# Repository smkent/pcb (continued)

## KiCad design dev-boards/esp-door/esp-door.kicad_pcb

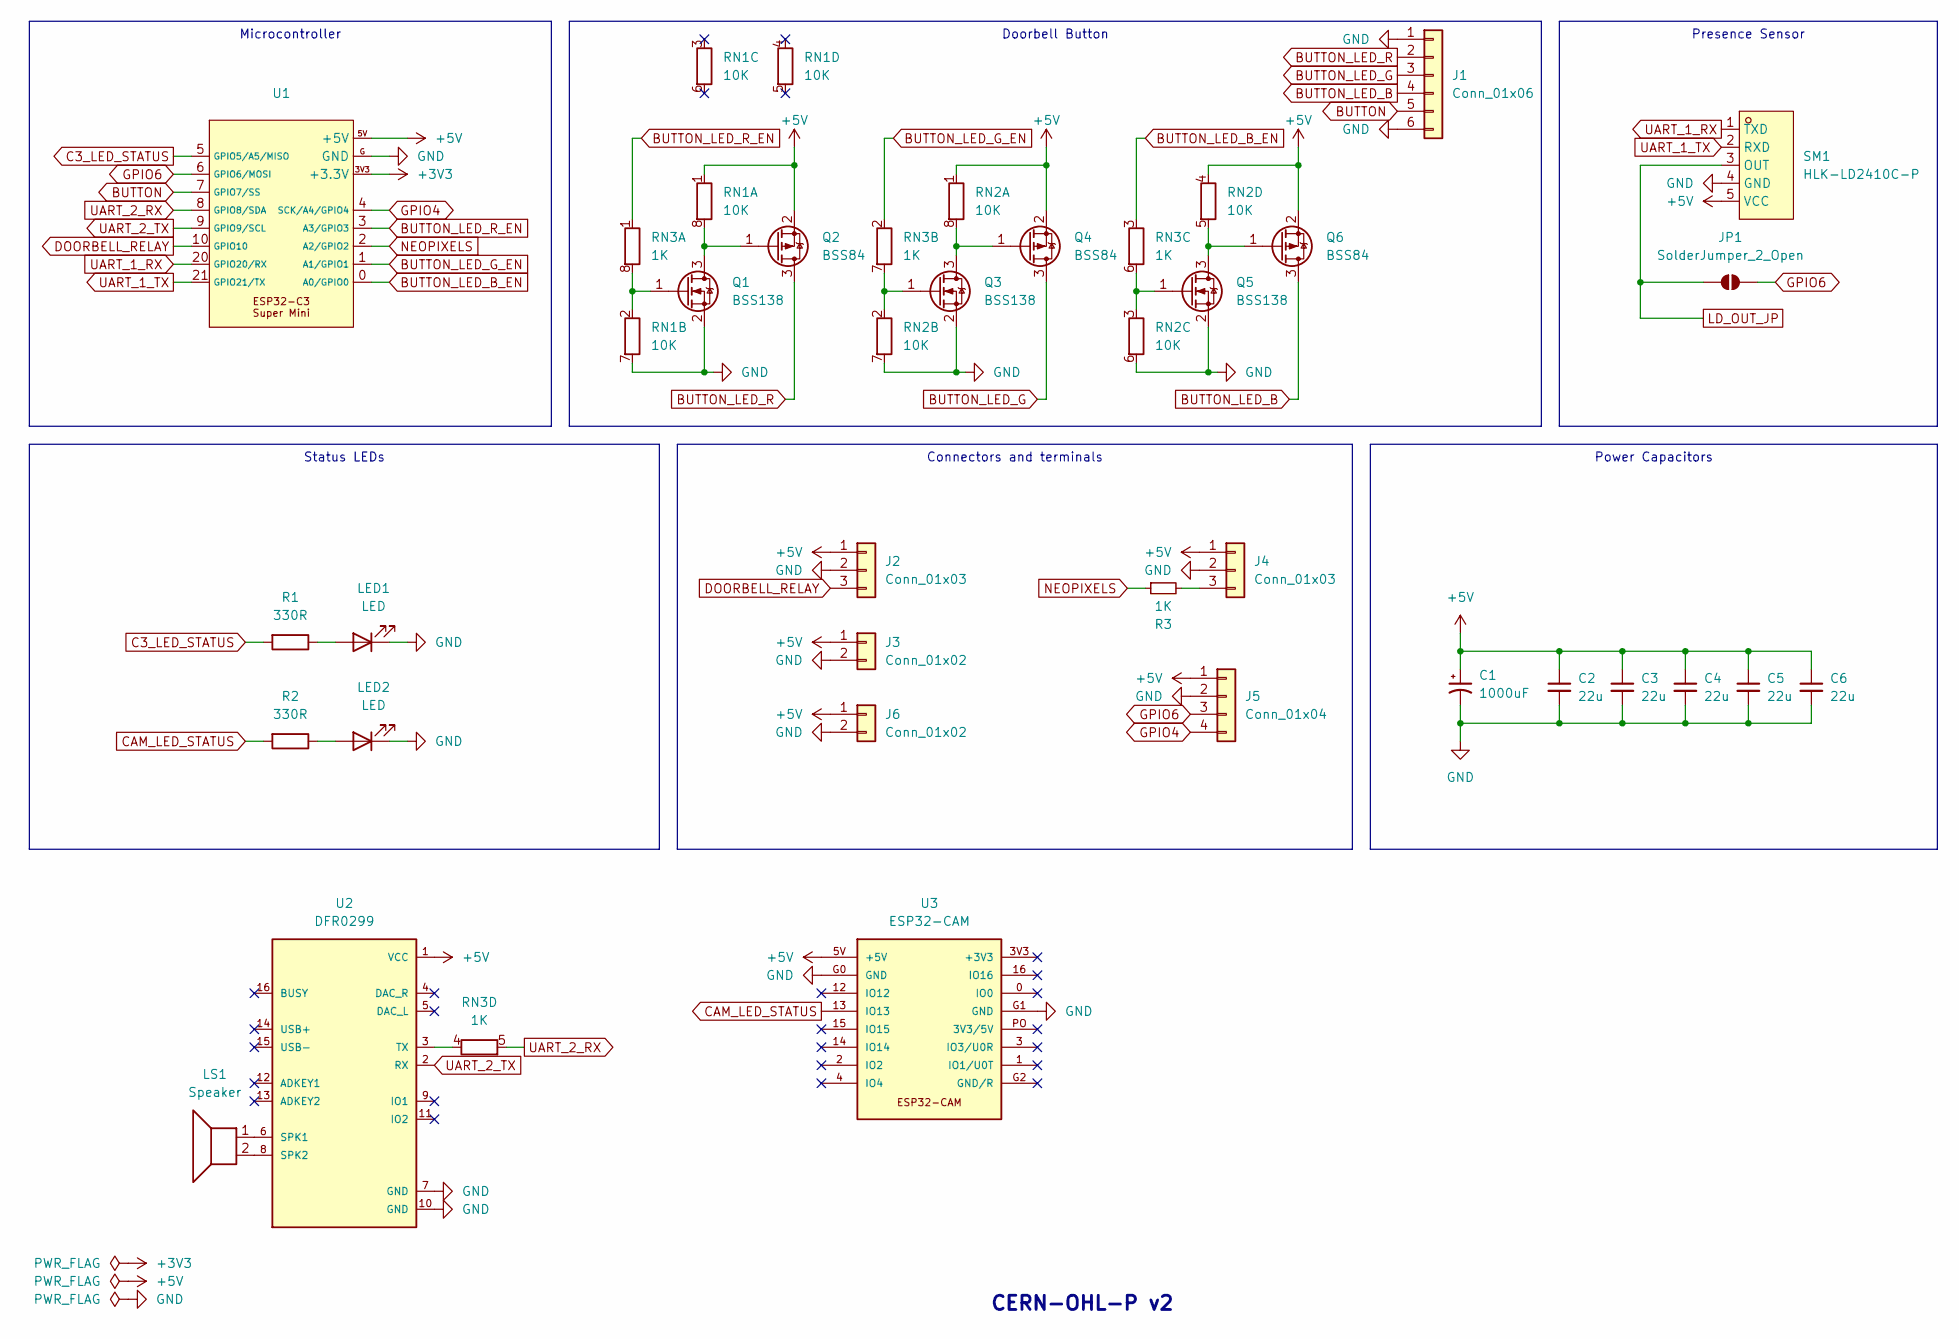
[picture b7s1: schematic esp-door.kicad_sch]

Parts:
C1: 1000uF; CP_Elec_8x10.5
C2, C3, C4, C5, C6: 22u; C_1206_3216Metric_Pad1.33x1.80mm_HandSolder
J1: Conn_01x06; JST_XH_S6B-XH_1x06_P2.50mm_Horizontal
J2, J4: Conn_01x03; JST_XH_S3B-XH_1x03_P2.50mm_Horizontal_pad2gnd
J3: Conn_01x02; JST_XH_S2B-XH_1x02_P2.50mm_Horizontal
J5: Conn_01x04; SurfacePads_1x04_P2.54mm_pad2gnd
J6: Conn_01x02; SurfacePads_1x02_P2.54mm_pad2gnd
JP1: SolderJumper_2_Open; SolderJumper-2_P1.3mm_Open_TrianglePad1.0x1.5mm
LED1, LED2: LED; LED_0805_2012Metric_Pad1.15x1.40mm_HandSolder_simple
LS1: Speaker; JST_XH_S2B-XH_1x02_P2.50mm_Horizontal
Q1, Q3, Q5: BSS138; SOT-23_simple
Q2, Q4, Q6: BSS84; SOT-23_simple
R1, R2: 330R; R_0805_2012Metric_Pad1.20x1.40mm_HandSolder
R3: 1K; R_0805_2012Metric_Pad1.20x1.40mm_HandSolder
RN1, RN2: 10K; R_Array_Convex_4x0603
RN3: 1K; R_Array_Convex_4x0603
SM1: HLK-LD2410C-P; SENSOR-TH_HLK-LD2410C-P; LCSC Part C19723500
U1: ESP32-C3-Super-Mini-Castellated-SMD
U2: DFR0299; DFPlayer-Mini-DFR0299-module
U3: ESP32-CAM

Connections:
+3V3: U1.3V3 (+3.3V)
+5V: C1.1, C2.1, C3.1, C4.1, C5.1, C6.1, J2.1, J3.1, J4.1, J5.1, J6.1, Q2.2 (S), Q4.2 (S), Q6.2 (S), RN1.1 (R1.1), RN2.1 (R1.1), RN2.4 (R4.1), SM1.5 (VCC), U1.5V (+5V), U2.1 (VCC), U3.5V (+5V)
BUTTON: J1.5, U1.7 (GPIO7/SS)
BUTTON_LED_B: J1.4, Q6.3 (D)
BUTTON_LED_B_EN: RN3.3 (R3.1), U1.0 (A0/GPIO0)
BUTTON_LED_G: J1.3, Q4.3 (D)
BUTTON_LED_G_EN: RN3.2 (R2.1), U1.1 (A1/GPIO1)
BUTTON_LED_R: J1.2, Q2.3 (D)
BUTTON_LED_R_EN: RN3.1 (R1.1), U1.3 (A3/GPIO3)
C3_LED_STATUS: R1.2, U1.5 (GPIO5/A5/MISO)
CAM_LED_STATUS: R2.2, U3.13 (IO13)
DOORBELL_RELAY: J2.3, U1.10 (GPIO10)
GND: C1.2, C2.2, C3.2, C4.2, C5.2, C6.2, J1.1, J1.6, J2.2, J3.2, J4.2, J5.2, J6.2, LED1.1 (K), LED2.1 (K), Q1.2 (S), Q3.2 (S), Q5.2 (S), RN1.7 (R2.2), RN2.6 (R3.2), RN2.7 (R2.2), SM1.4 (GND), U1.G (GND), U2.7 (GND), U2.10 (GND), U3.G0 (GND), U3.G1 (GND)
GPIO4: J5.4, U1.4 (SCK/A4/GPIO4)
GPIO6: J5.3, JP1.2 (B), U1.6 (GPIO6/MOSI)
LD_OUT_JP: JP1.1 (A), SM1.3 (OUT)
NEOPIXELS: R3.1, U1.2 (A2/GPIO2)
unnamed: J4.3, R3.2
unnamed: LED1.2 (A), R1.1
unnamed: LED2.2 (A), R2.1
unnamed: Q1.3 (D), Q2.1 (G), RN1.8 (R1.2)
unnamed: Q1.1 (G), RN1.2 (R2.1), RN3.8 (R1.2)
unnamed: Q3.3 (D), Q4.1 (G), RN2.8 (R1.2)
unnamed: Q3.1 (G), RN2.2 (R2.1), RN3.7 (R2.2)
unnamed: Q5.3 (D), Q6.1 (G), RN2.5 (R4.2)
unnamed: Q5.1 (G), RN2.3 (R3.1), RN3.6 (R3.2)
unnamed: RN3.4 (R4.1), U2.3 (TX)
unnamed: LS1.1, U2.6 (SPK1)
unnamed: LS1.2, U2.8 (SPK2)
UART_1_RX: SM1.1 (TXD), U1.20 (GPIO20/RX)
UART_1_TX: SM1.2 (RXD), U1.21 (GPIO21/TX)
UART_2_RX: RN3.5 (R4.2), U1.8 (GPIO8/SDA)
UART_2_TX: U1.9 (GPIO9/SCL), U2.2 (RX)

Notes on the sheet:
Microcontroller
Doorbell Button
Presence Sensor
Status LEDs
Power Capacitors
Connectors and terminals
CERN-OHL-P v2

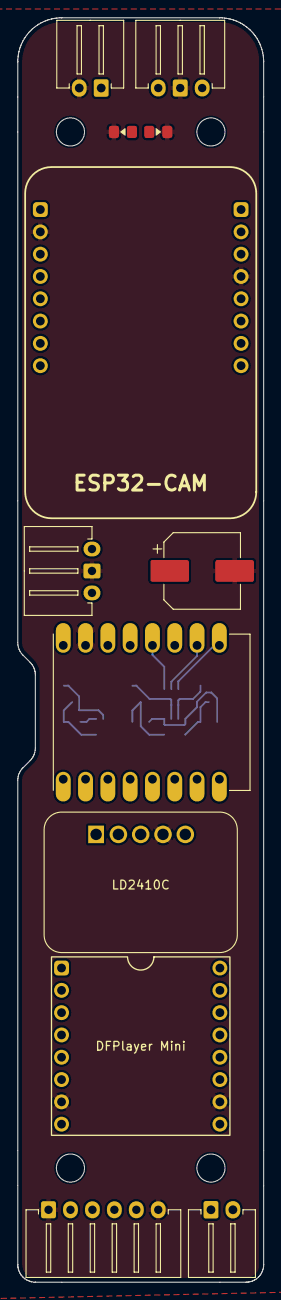
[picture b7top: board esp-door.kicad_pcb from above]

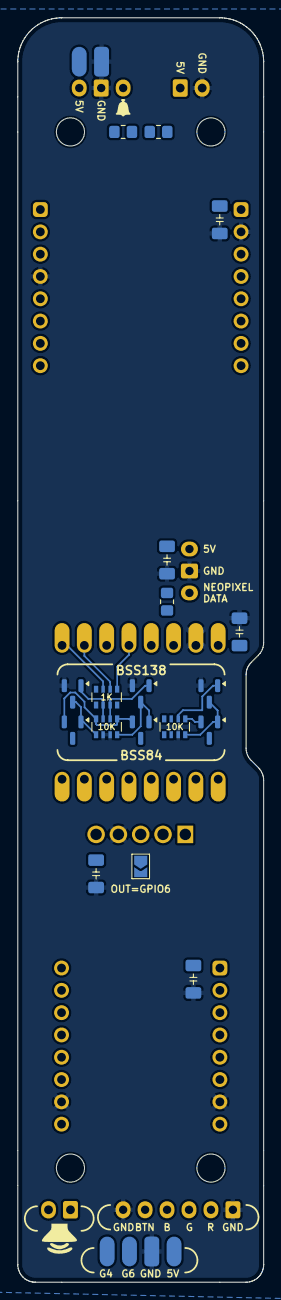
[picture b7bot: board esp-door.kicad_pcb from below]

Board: 2 copper layers, 28.0 x 144.0 mm, 32 parts (20 on the bottom side), 32 nets.
